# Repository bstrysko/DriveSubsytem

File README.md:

DriveSubsytem
=============

Drive Subsystem for Robotics Applications

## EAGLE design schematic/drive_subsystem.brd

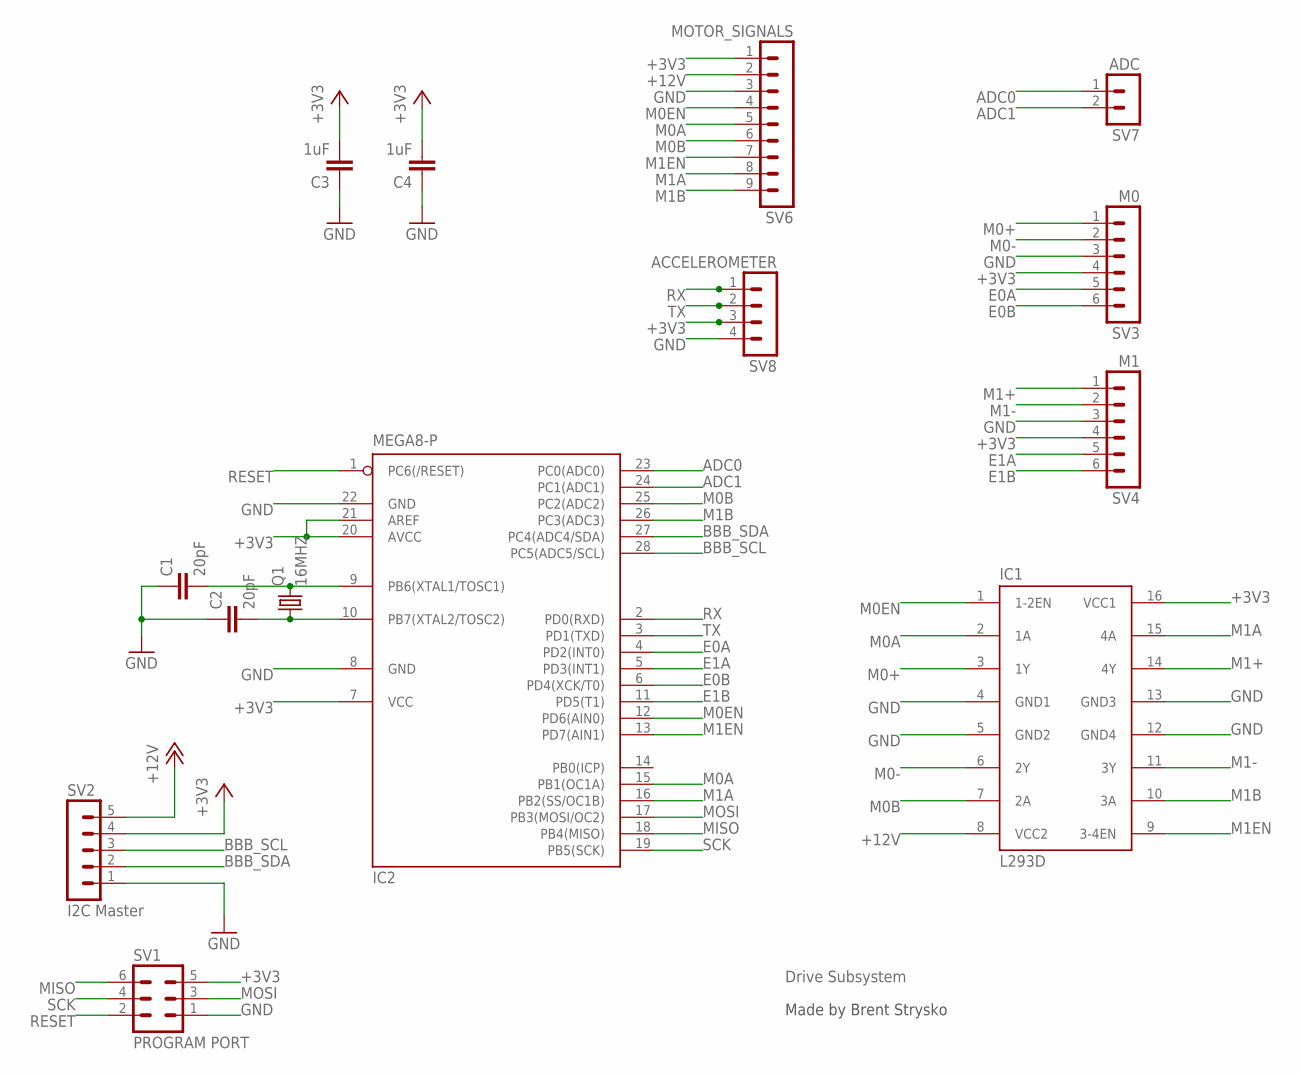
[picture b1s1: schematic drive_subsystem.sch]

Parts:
C1, C2: 20pF; CAP-PTH-SMALL-KIT
C3, C4: 1uF; CAP-PTH-SMALL-KIT
IC1: L293D; DIL16
IC2: MEGA8-P; DIL28-3
Q1: 16MHZ; HC49U-V
SV1: PROGRAM PORT; MA03-2
SV2: I2C Master; MA05-1
SV3: M0; MA06-1
SV4: M1; MA06-1
SV6: MOTOR_SIGNALS; MA09-1
SV7: ADC; MA02-1
SV8: ACCELEROMETER; MA04-1

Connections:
+3V3: C3.2, C4.2, IC1.16 (VCC1), IC2.7 (VCC), IC2.20 (AVCC), IC2.21 (AREF), SV1.5, SV2.4, SV3.4, SV4.4, SV6.1, SV8.3
+12V: IC1.8 (VCC2), SV2.5, SV6.2
ADC0: IC2.23 (PC0(ADC0)), SV7.1
ADC1: IC2.24 (PC1(ADC1)), SV7.2
BBB_SCL: IC2.28 (PC5(ADC5/SCL)), SV2.3
BBB_SDA: IC2.27 (PC4(ADC4/SDA)), SV2.2
E0A: IC2.4 (PD2(INT0)), SV3.5
E0B: IC2.6 (PD4(XCK/T0)), SV3.6
E1A: IC2.5 (PD3(INT1)), SV4.5
E1B: IC2.11 (PD5(T1)), SV4.6
GND: C1.1, C2.1, C3.1, C4.1, IC1.4 (GND1), IC1.5 (GND2), IC1.12 (GND4), IC1.13 (GND3), IC2.8 (GND), IC2.22 (GND), SV1.1, SV2.1, SV3.3, SV4.3, SV6.3, SV8.4
M0+: IC1.3 (1Y), SV3.1
M0-: IC1.6 (2Y), SV3.2
M0A: IC1.2 (1A), IC2.15 (PB1(OC1A)), SV6.5
M0B: IC1.7 (2A), IC2.25 (PC2(ADC2)), SV6.6
M0EN: IC1.1 (1-2EN), IC2.12 (PD6(AIN0)), SV6.4
M1+: IC1.14 (4Y), SV4.1
M1-: IC1.11 (3Y), SV4.2
M1A: IC1.15 (4A), IC2.16 (PB2(SS/OC1B)), SV6.8
M1B: IC1.10 (3A), IC2.26 (PC3(ADC3)), SV6.9
M1EN: IC1.9 (3-4EN), IC2.13 (PD7(AIN1)), SV6.7
MISO: IC2.18 (PB4(MISO)), SV1.6
MOSI: IC2.17 (PB3(MOSI/OC2)), SV1.3
RESET: IC2.1 (PC6(/RESET)), SV1.2
RX: IC2.2 (PD0(RXD)), SV8.1
SCK: IC2.19 (PB5(SCK)), SV1.4
TX: IC2.3 (PD1(TXD)), SV8.2
XTAL1: C1.2, IC2.9 (PB6(XTAL1/TOSC1)), Q1.2
XTAL2: C2.2, IC2.10 (PB7(XTAL2/TOSC2)), Q1.1

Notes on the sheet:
Made by Brent Strysko
Drive Subsystem

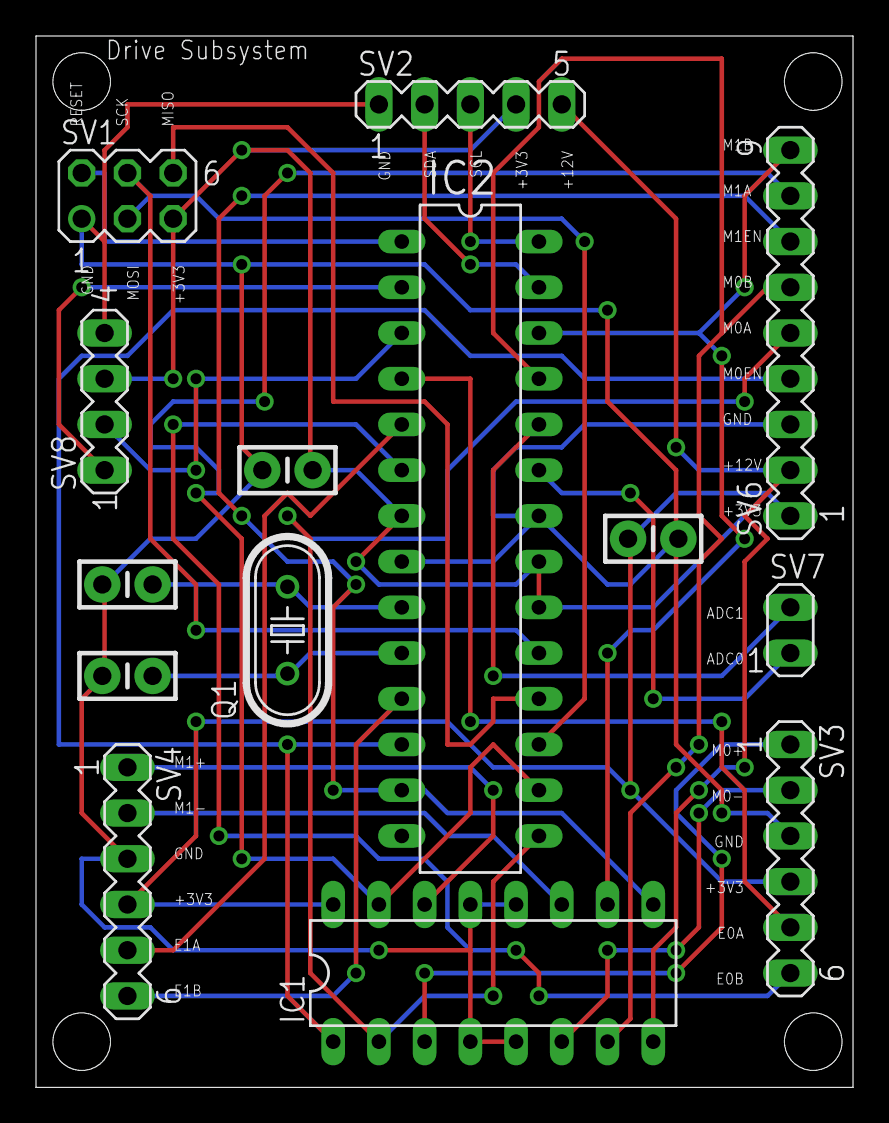
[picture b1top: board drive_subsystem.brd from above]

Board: 2 copper layers, 45.4 x 58.4 mm, 14 parts (0 on the bottom side), 29 nets.

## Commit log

2014-02-01 Testing of motors
2014-03-25 Drive Subsystem Schematic and Board committed
2014-04-15 Created libMaster and test. Still need to implement firmware.
2014-04-15 Moved register definitions to seperate header
2014-04-16 Implemented motor functionality
2014-04-16 Switched communication to new protocol using floats instead of a byte over the bus

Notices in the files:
parts and their libraries:
SparkFun-Capacitors: Licensing: CC v3.0 Share-Alike You are welcome to use this library for commercial purposes.
hypertriangle: Copyright HyperTriangle 2010-2011
